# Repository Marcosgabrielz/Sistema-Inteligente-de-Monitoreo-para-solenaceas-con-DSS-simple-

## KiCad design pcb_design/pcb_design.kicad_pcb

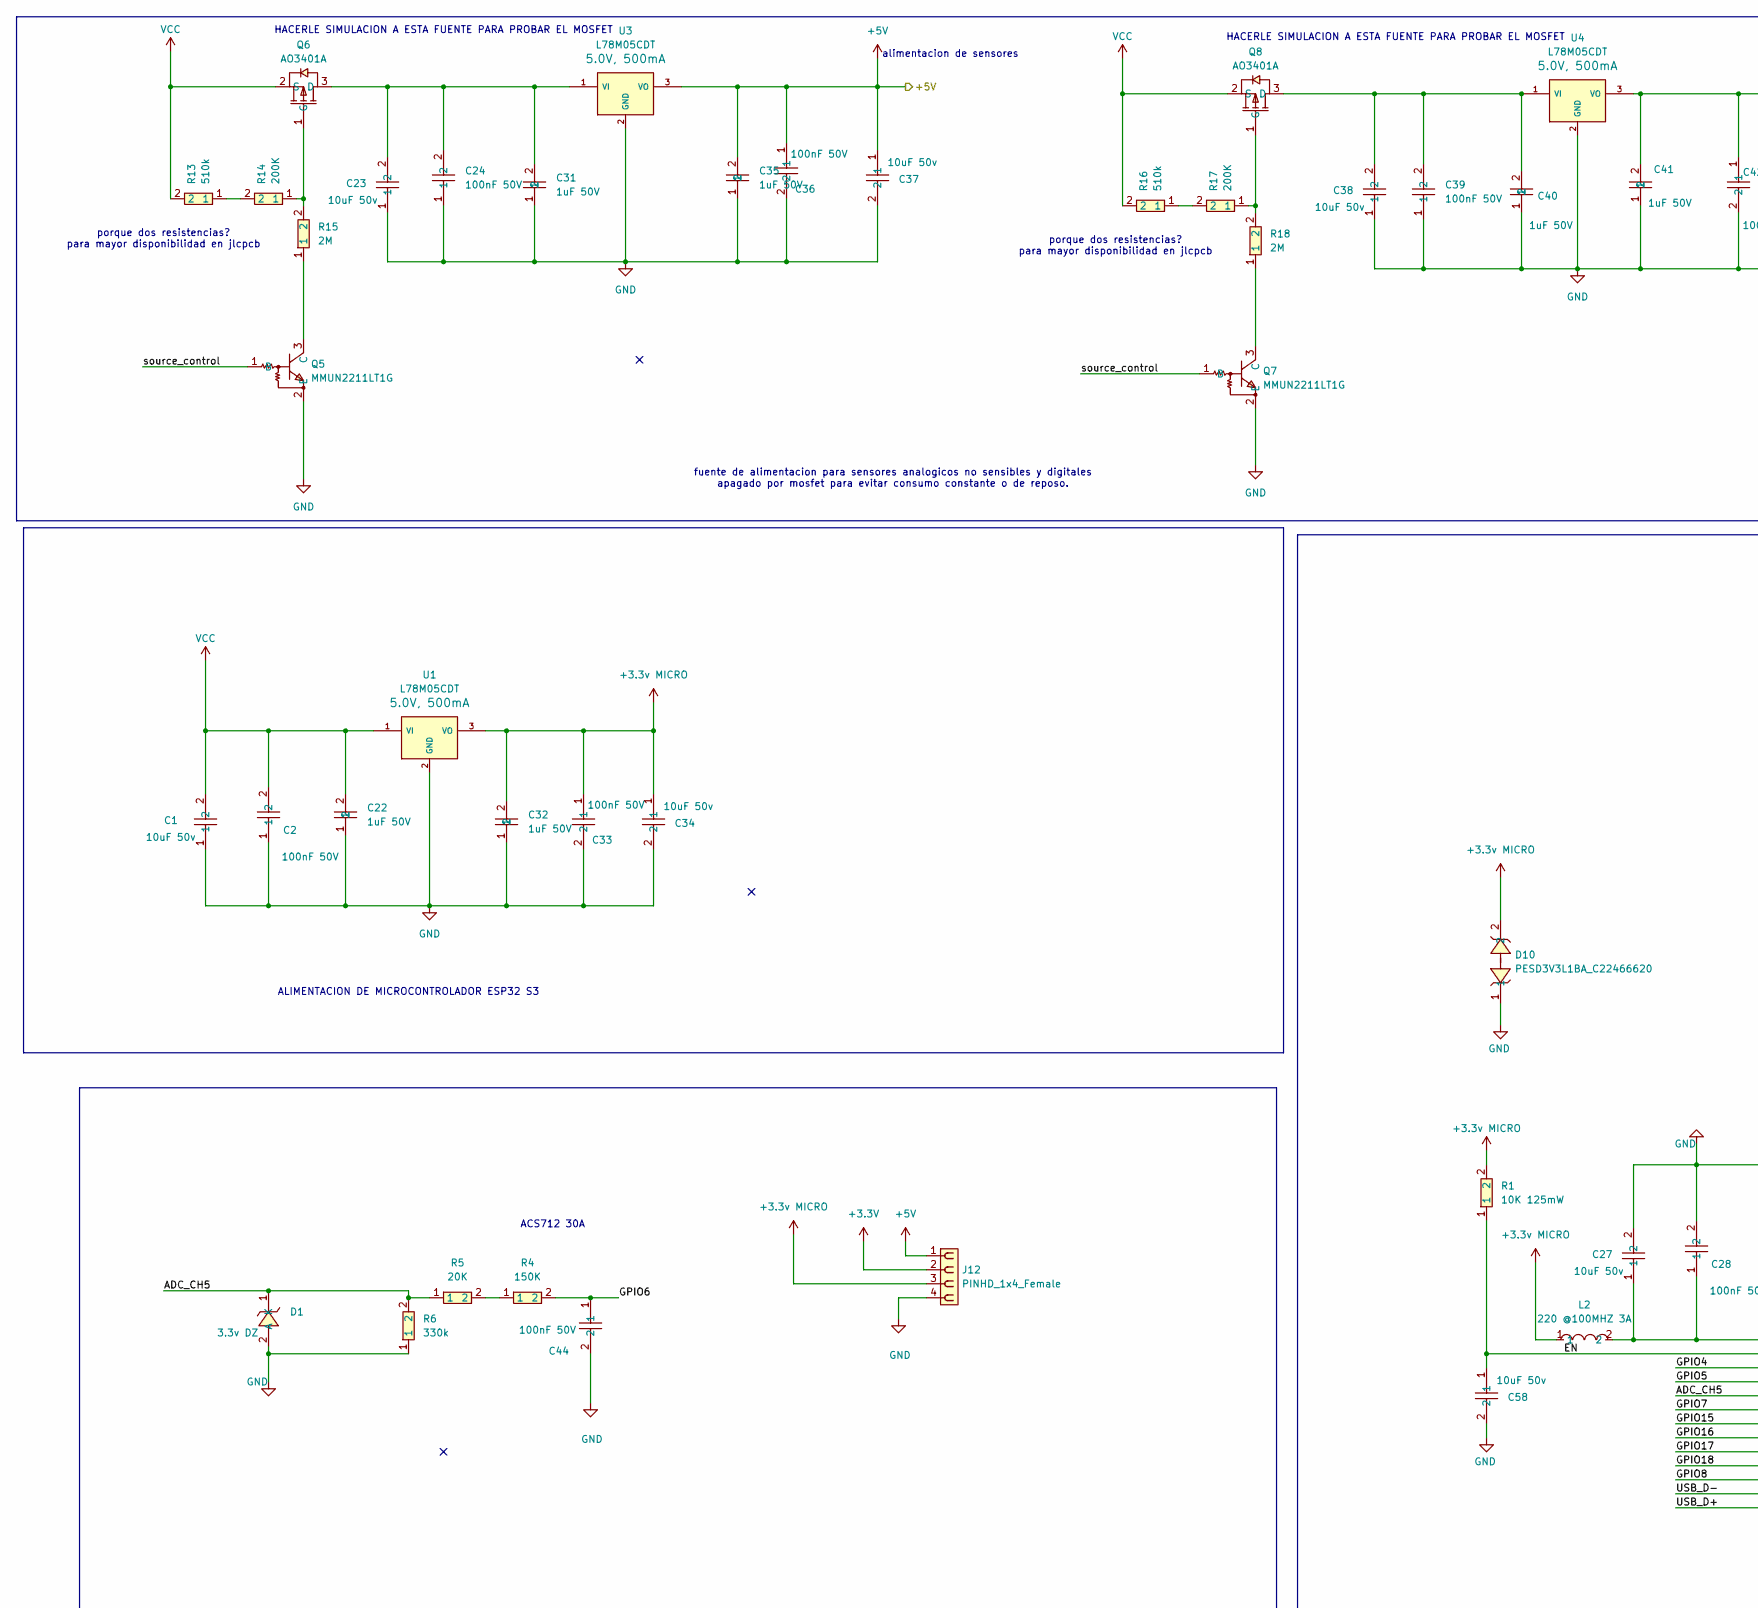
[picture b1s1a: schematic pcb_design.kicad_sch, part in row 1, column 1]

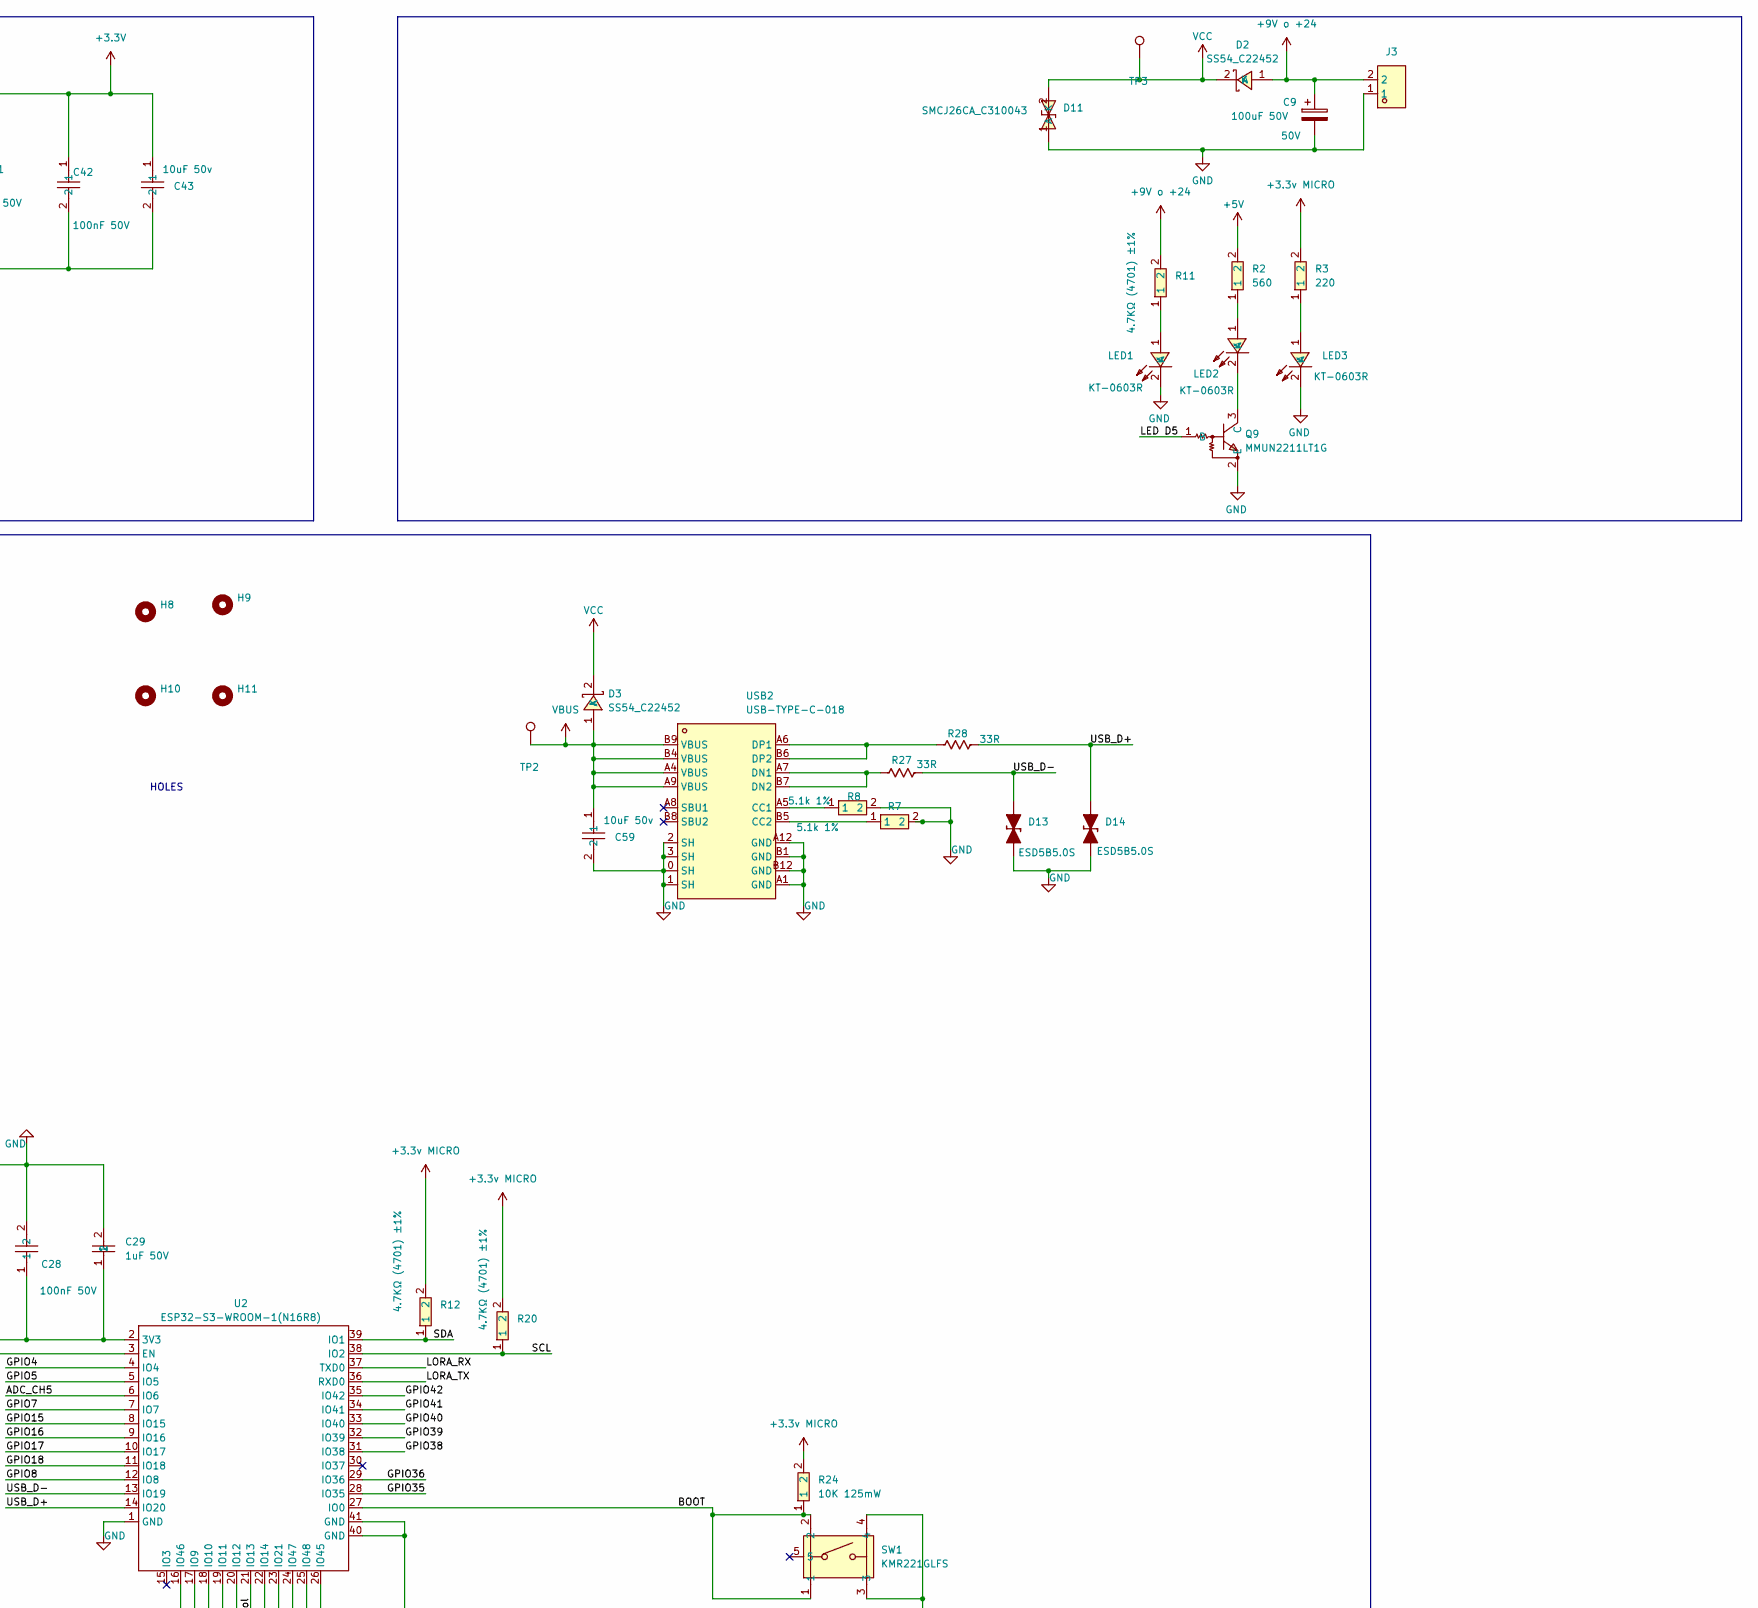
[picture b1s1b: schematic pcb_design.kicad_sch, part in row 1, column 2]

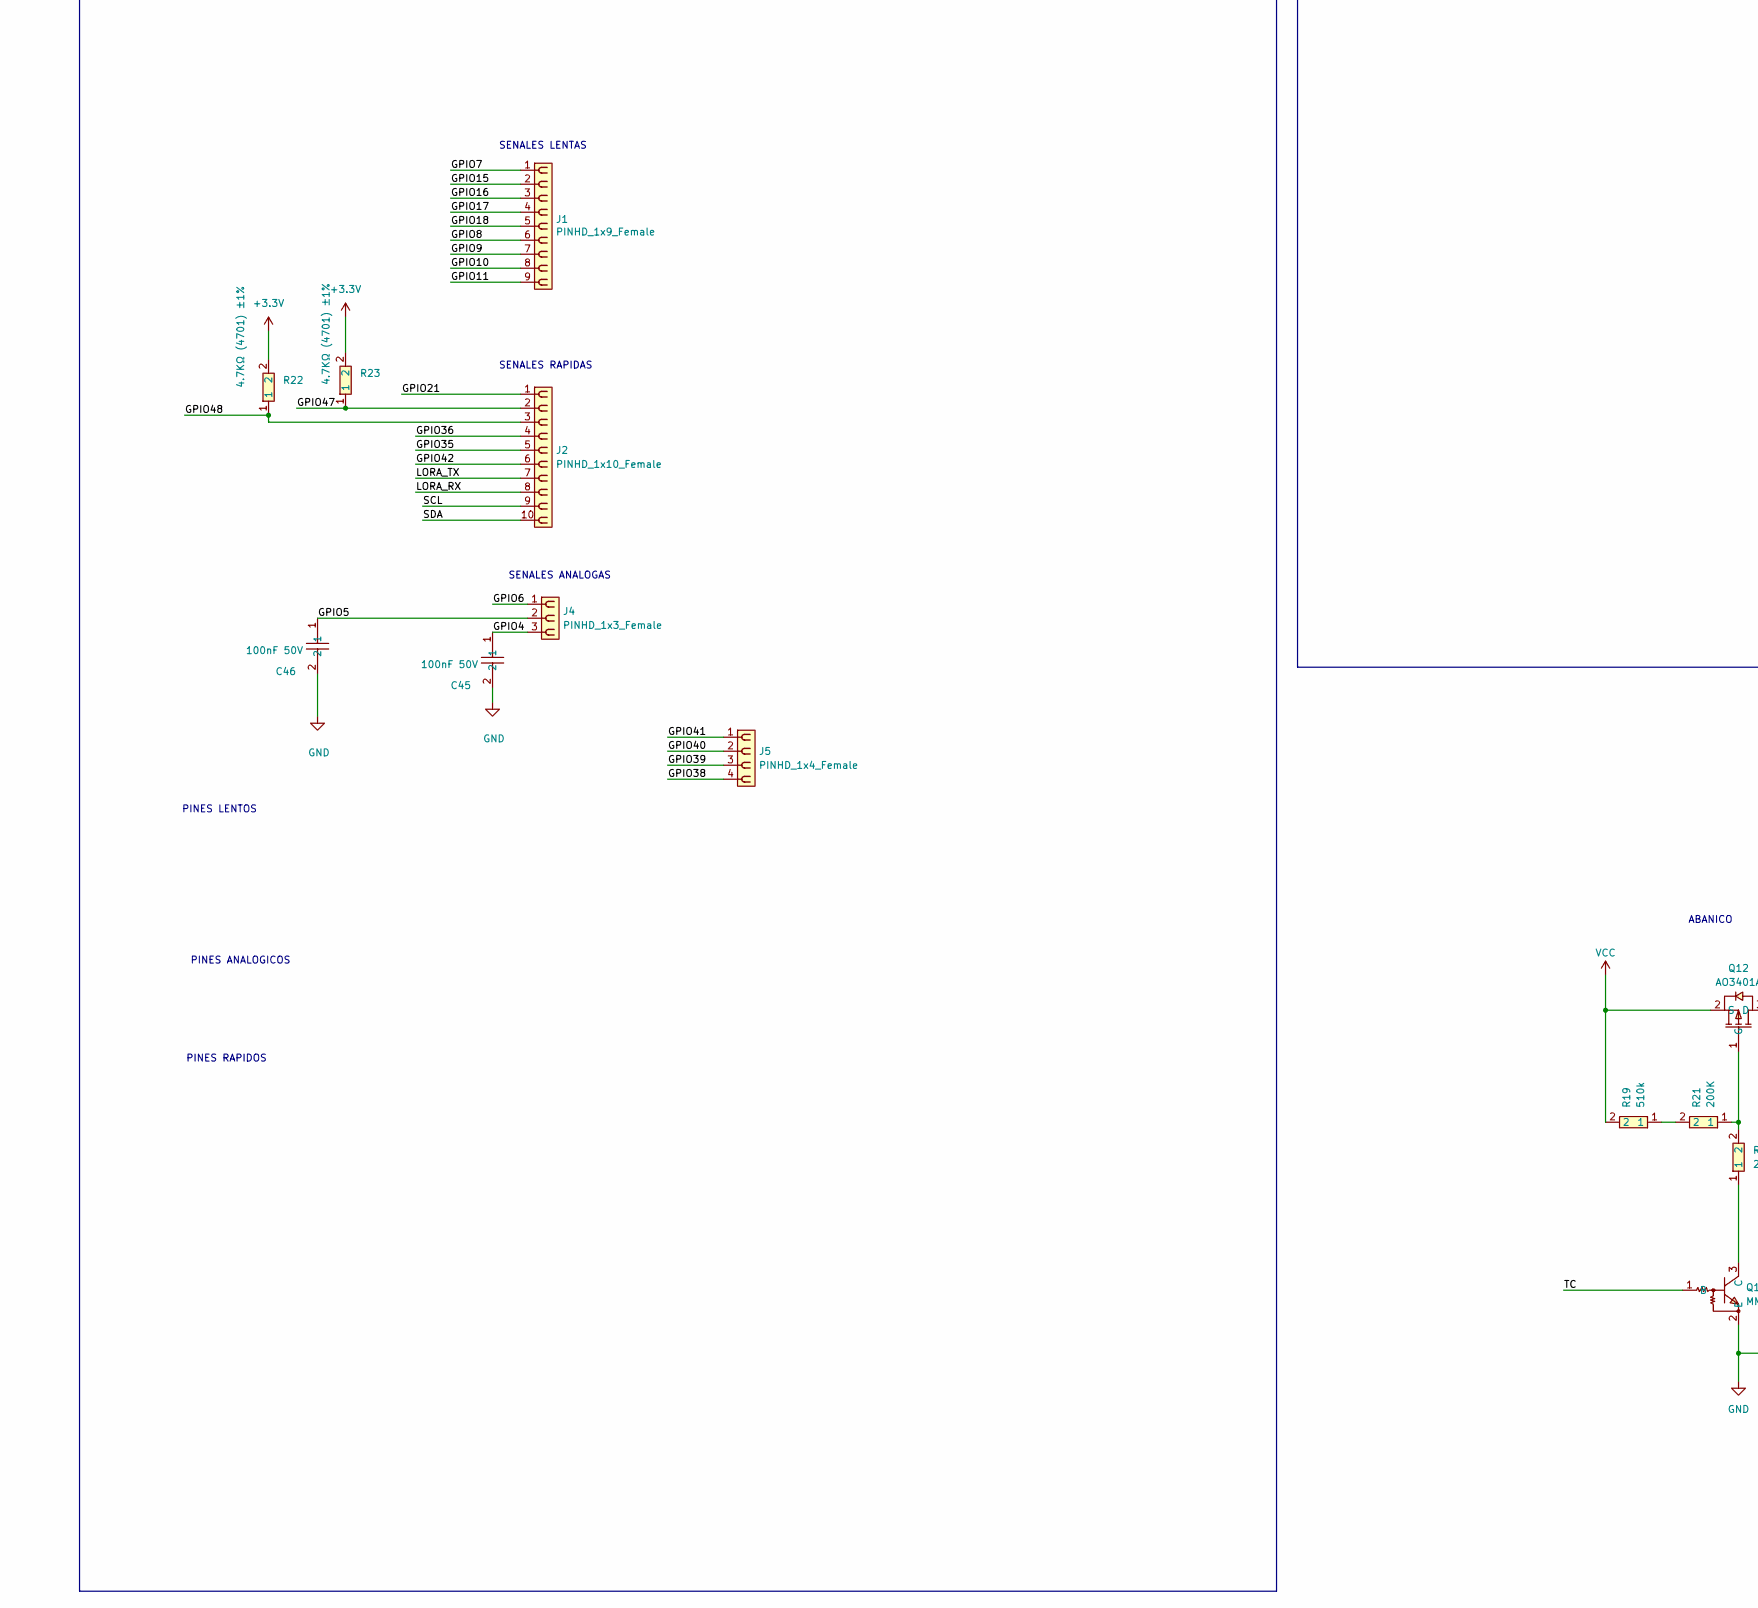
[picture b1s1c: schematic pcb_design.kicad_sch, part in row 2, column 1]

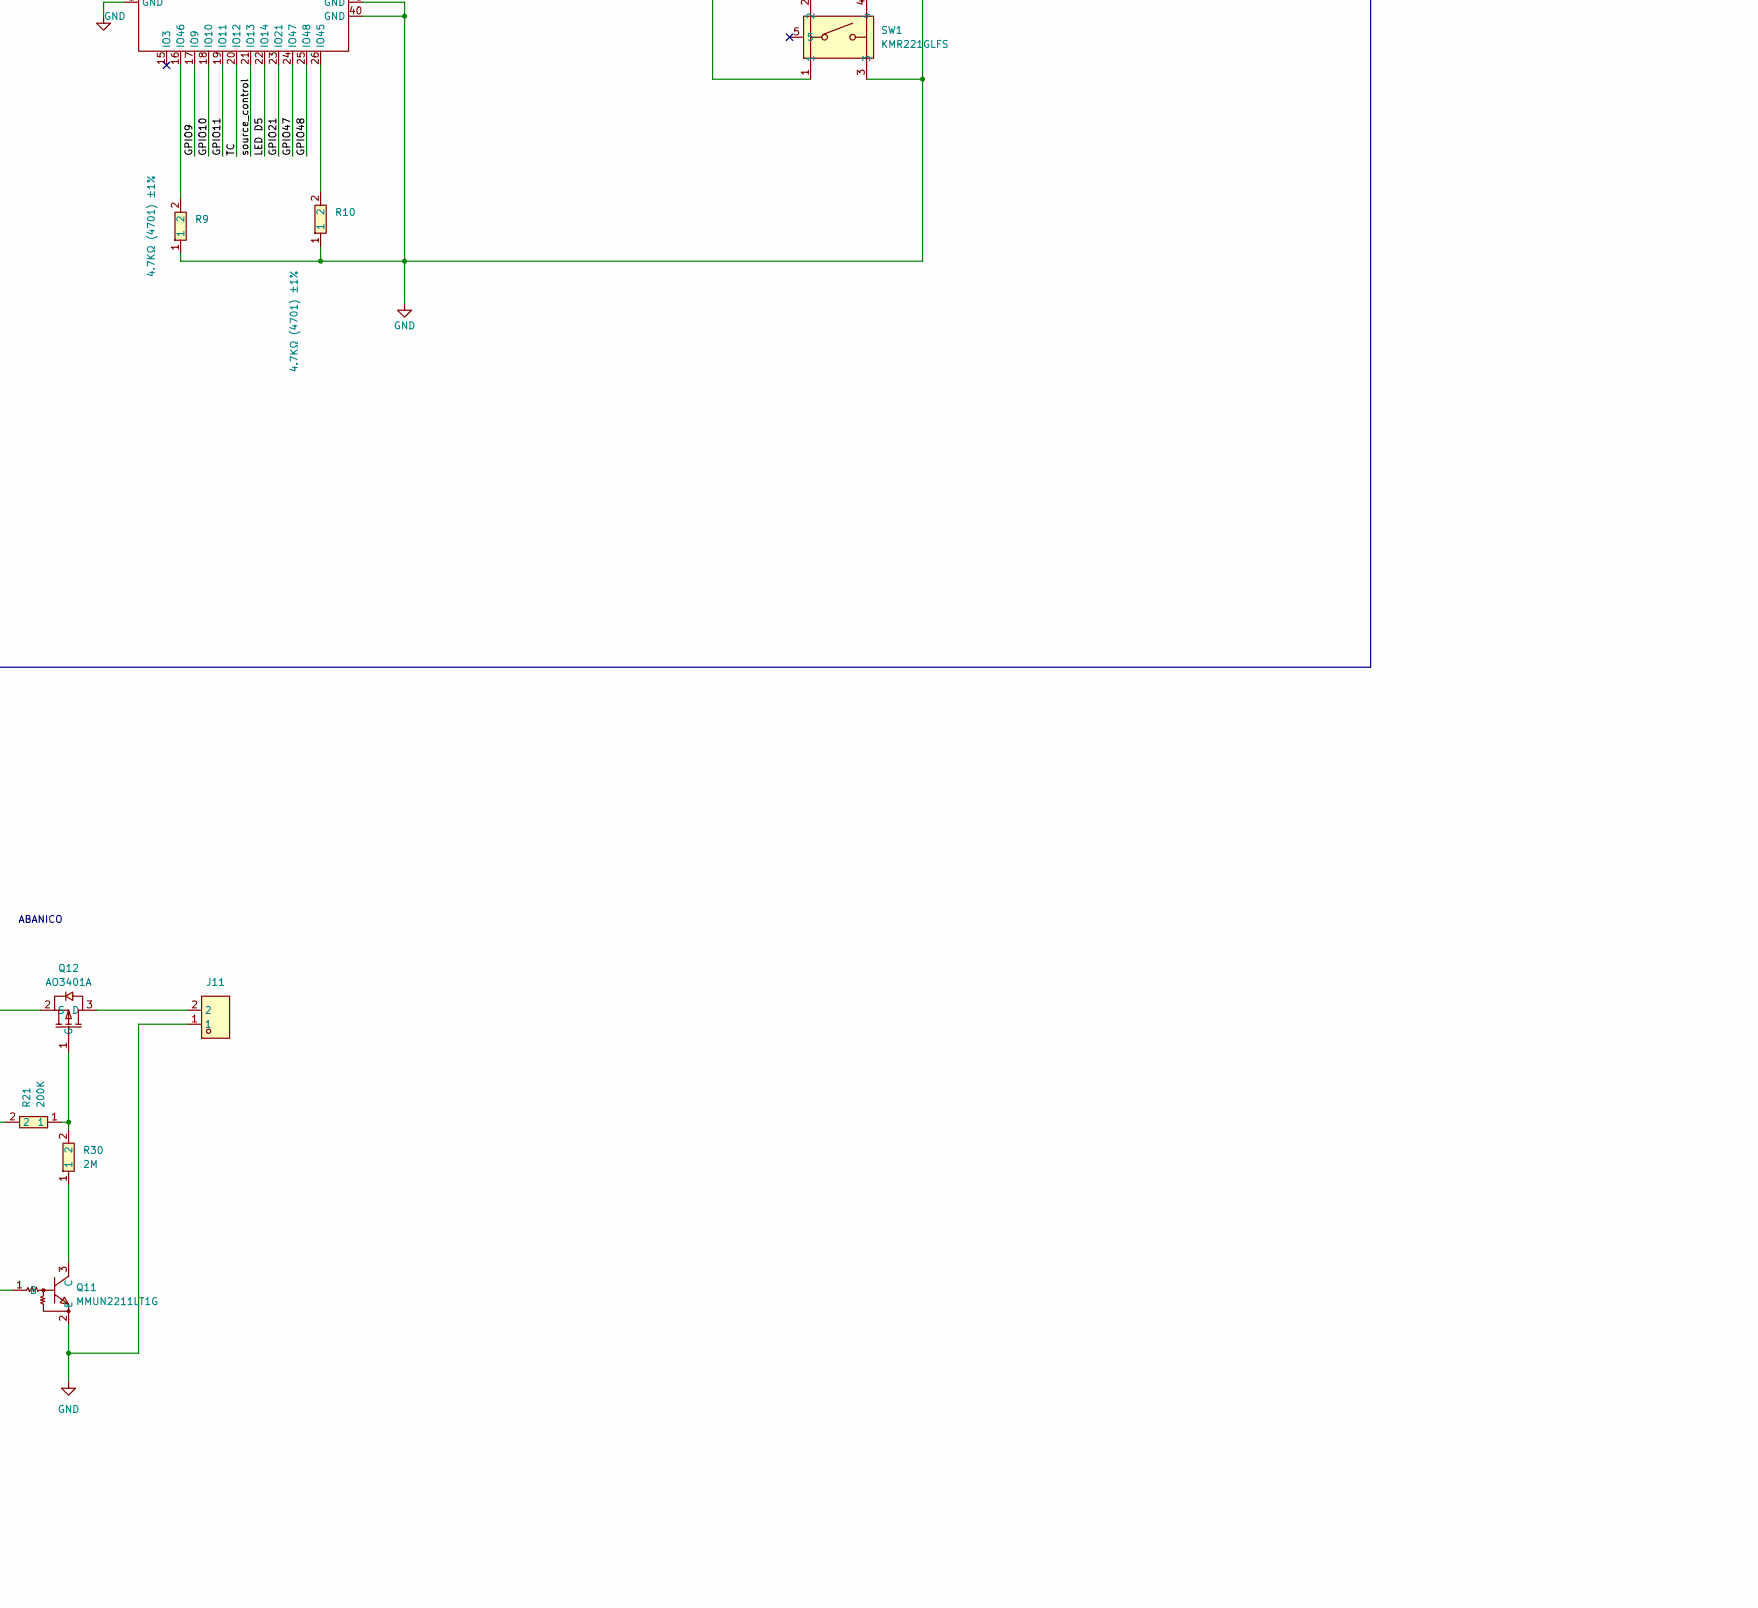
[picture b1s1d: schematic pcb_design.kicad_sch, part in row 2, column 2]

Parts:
C1, C23, C27, C34, C37, C38, C43, C58, C59: 10uF 50v; C0805; MPN GRM21BR61H106KE43L; LCSC Part C440198
C2, C24, C28, C33, C36, C39, C42, C44, C45, C46: 100nF 50V; C0603; MPN CC0603KRX7R9BB104; LCSC Part C14663
C9: 100uF 50V; CP_Radial_D5.0mm_P2.50mm; LCSC Part C3151829
C22, C29, C31, C32, C35, C40, C41: 1uF 50V; C0805; MPN CL21B105KBFNNNE; LCSC Part C28323
D1: MMSZ5226B_C19077421; SOD-123_L2.7-W1.6-LS3.7-RD; MPN MMSZ5226B; LCSC Part C19077421
D2, D3: SS54_C22452; SMA_L4.4-W2.8-LS5.4-R-RD; MPN SS54; LCSC Part C22452
D10: PESD3V3L1BA_C22466620; SOD-323_L1.7-W1.3-LS2.6-BI; MPN PESD3V3L1BA; LCSC Part C22466620
D11: SMCJ26CA_C310043; SMC_L6.9-W5.9-LS7.9-BI; MPN SMCJ26CA/TR13; LCSC Part C310043
D13, D14: ESD5B5.0S; D_SOD-523; LCSC Part C93623
H8, H9, H10, H11: MountingHole; MountingHole_2-56
J1: PINHD_1x9_Female; 1x09_P2.54mm
J2: PINHD_1x10_Female; 1x10_P2.54mm
J3: DB128L-5.08-2P-BK-S; ScrewTerminal_1x02_P5.0mm; LCSC Part C430601
J4: PINHD_1x3_Female; 1x03_P2.54mm
J5, J12: PINHD_1x4_Female; 1x04_P2.54mm
J11: DB128L-5.08-2P-BK-S; 1x02_P2.54mm; LCSC Part C430601
L2: 220 @100MHZ 3A; L0805; MPN MPZ2012S221AT000; LCSC Part C76818
LED1, LED2, LED3: KT-0603R; LED-SMD_L1.6-W0.8-R-RD; MPN KT-0603R; LCSC Part C2286
Q5, Q7, Q9, Q11: MMUN2211LT1G; SOT-23-3_L2.9-W1.6-P1.90-LS2.8-BR; MPN MMUN2211LT1G; LCSC Part C55059
Q6, Q8, Q12: AO3401A; SOT-23_L2.9-W1.3-P1.90-LS2.4-BR; MPN AO3401A; LCSC Part C15127
R1, R24: 10K 125mW; R0805; MPN 0805W8F1002T5E; LCSC Part C17414
R2: 560; R0603; MPN 0603WAF5600T5E; LCSC Part C23204
R3: 220; R0805; MPN 0805W8F2200T5E; LCSC Part C17557
R4: 150K; R0805; MPN 0805W8F1503T5E; LCSC Part C17470
R5: 20K; R0603; MPN 0603WAF2002T5E; LCSC Part C4184
R6: 330k; R0603; MPN 0603WAF3303T5E; LCSC Part C23137
R7, R8: FRC0603F5101TS; R0603; MPN FRC0603F5101TS; LCSC Part C2907044
R9, R10, R11, R12, R20, R22, R23: 0603WAF4701T5E; R0603; MPN 0603WAF4701T5E; LCSC Part C23162
R13, R16, R19: 510k; R0603; MPN 0603WAF5103T5E; LCSC Part C23192
R14, R17, R21: 200K; R0603; MPN 0603WAF2003T5E; LCSC Part C25811
R15, R18, R30: 2M; R0603; MPN 0603WAF2004T5E; LCSC Part C22976
R27, R28: 33R; R_0603_1608Metric; LCSC Part C126353
SW1: KMR221GLFS; KEY-SMD_KMR2XXGXXX; MPN KMR221GLFS; LCSC Part C72443
TP2, TP3: TestPoint_Hole1; TestPoint_WireHole
U1, U3, U4: L78M05CDT; TO-220-3_Vertical; Part Number L78M05CDT-TR; JLCPCB ID C58069
U2: ESP32-S3-WROOM-1(N16R8); WIRELM-SMD_ESP32-S3-WROOM-1; LCSC Part C2913204
USB2: USB-TYPE-C-018; USB-C_SMD-TYPE-C-31-M-12; MPN USB-TYPE-C-018; LCSC Part C2927038

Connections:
+3.3V: C41.2, C42.1, C43.1, J12.2, R22.2, R23.2, U4.3 (VO)
+3.3v MICRO: C32.2, C33.1, C34.1, D10.2, J12.3, L2.1, R1.2, R3.2, R12.2, R20.2, R24.2, U1.3 (VO)
+5V: C35.2, C36.1, C37.1, J12.1, R2.2, U3.3 (VO)
+9V o +24: C9.1, D2.1 (A), J3.2, R11.2
/ADC_CH5: D1.1 (K), R5.1, R6.2, U2.6 (IO6)
/BOOT: R24.1, SW1.1, SW1.2, U2.27 (IO0)
/EN: C58.1, R1.1, U2.3 (EN)
/GPIO4: C45.1, J4.3, U2.4 (IO4)
/GPIO5: C46.1, J4.2, U2.5 (IO5)
/GPIO6: C44.1, J4.1, R4.2
/GPIO7: J1.1, U2.7 (IO7)
/GPIO8: J1.6, U2.12 (IO8)
/GPIO9: J1.7, U2.17 (IO9)
/GPIO10: J1.8, U2.18 (IO10)
/GPIO11: J1.9, U2.19 (IO11)
/GPIO15: J1.2, U2.8 (IO15)
/GPIO16: J1.3, U2.9 (IO16)
/GPIO17: J1.4, U2.10 (IO17)
/GPIO18: J1.5, U2.11 (IO18)
/GPIO21: J2.1, U2.23 (IO21)
/GPIO35: J2.5, U2.28 (IO35)
/GPIO36: J2.4, U2.29 (IO36)
/GPIO38: J5.4, U2.31 (IO38)
/GPIO39: J5.3, U2.32 (IO39)
/GPIO40: J5.2, U2.33 (IO40)
/GPIO41: J5.1, U2.34 (IO41)
/GPIO42: J2.6, U2.35 (IO42)
/GPIO47: J2.2, R23.1, U2.24 (IO47)
/GPIO48: J2.3, R22.1, U2.25 (IO48)
/LED D5: Q9.1 (B), U2.22 (IO14)
/LORA_RX: J2.8, U2.37 (TXD0)
/LORA_TX: J2.7, U2.36 (RXD0)
/SCL: J2.9, R20.1, U2.38 (IO2)
/SDA: J2.10, R12.1, U2.39 (IO1)
/TC: Q11.1 (B), U2.20 (IO12)
/USB_D+: D14.2 (A), R28.2, U2.14 (IO20)
/USB_D-: D13.2 (A), R27.2, U2.13 (IO19)
/source_control: Q5.1 (B), Q7.1 (B), U2.21 (IO13)
GND: C1.1, C2.1, C9.2, C22.1, C23.1, C24.1, C27.2, C28.2, C29.2, C31.1, C32.1, C33.2, C34.2, C35.1, C36.2, C37.2, C38.1, C39.1, C40.1, C41.1, C42.2, C43.2, C44.2, C45.2, C46.2, C58.2, C59.2, D1.2 (A), D10.1, D11.1 (K), D13.1 (K), D14.1 (K), J3.1, J11.1, J12.4, LED1.2 (K), LED3.2 (K), Q5.2 (E), Q7.2 (E), Q9.2 (E), Q11.2 (E), R6.1, R7.2, R8.2, R9.1, R10.1, SW1.3, SW1.4, U1.2 (GND), U2.1 (GND), U2.40 (GND), U2.41 (GND), U3.2 (GND), U4.2 (GND), USB2.0 (SH), USB2.1 (SH), USB2.2 (SH), USB2.3 (SH), USB2.A1 (GND), USB2.A12 (GND), USB2.B1 (GND), USB2.B12 (GND)
unnamed: LED1.1 (A), R11.1
unnamed: LED2.1 (A), R2.1
unnamed: LED2.2 (K), Q9.3 (C)
unnamed: LED3.1 (A), R3.1
unnamed: Q5.3 (C), R15.1
unnamed: C23.2, C24.2, C31.2, Q6.3 (D), U3.1 (VI)
unnamed: Q6.1 (G), R14.1, R15.2
unnamed: Q7.3 (C), R18.1
unnamed: C38.2, C39.2, C40.2, Q8.3 (D), U4.1 (VI)
unnamed: Q8.1 (G), R17.1, R18.2
unnamed: Q11.3 (C), R30.1
unnamed: J11.2, Q12.3 (D)
unnamed: Q12.1 (G), R21.1, R30.2
unnamed: R4.1, R5.2
unnamed: R13.1, R14.2
unnamed: R16.1, R17.2
unnamed: R19.1, R21.2
unnamed: C27.1, C28.1, C29.1, L2.2, U2.2 (3V3)
unnamed: R10.2, U2.26 (IO45)
unnamed: R9.2, U2.16 (IO46)
unnamed: R8.1, USB2.A5 (CC1)
unnamed: R7.1, USB2.B5 (CC2)
unnamed: R27.1, USB2.A7 (DN1), USB2.B7 (DN2)
unnamed: R28.1, USB2.A6 (DP1), USB2.B6 (DP2)
VBUS: C59.1, D3.1 (A), TP2.1 (1_1), USB2.A4 (VBUS), USB2.A9 (VBUS), USB2.B4 (VBUS), USB2.B9 (VBUS)
VCC: C1.2, C2.2, C22.2, D2.2 (K), D3.2 (K), D11.2 (A), Q6.2 (S), Q8.2 (S), Q12.2 (S), R13.2, R16.2, R19.2, TP3.1 (1_1), U1.1 (VI)

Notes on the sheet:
HOLES
HACERLE SIMULACION A ESTA FUENTE PARA PROBAR EL MOSFET
PINES ANALOGICOS
SENALES ANALOGAS
SENALES LENTAS
SENALES RAPIDAS
alimentacion de sensores
PINES LENTOS
ALIMENTACION DE MICROCONTROLADOR ESP32 S3
fuente de alimentacion para sensores analogicos no sensibles y digitales apagado por mosfet para evitar consumo constante o de reposo.
ACS712 30A
PINES RAPIDOS
porque dos resistencias? para mayor disponibilidad en jlcpcb
ABANICO

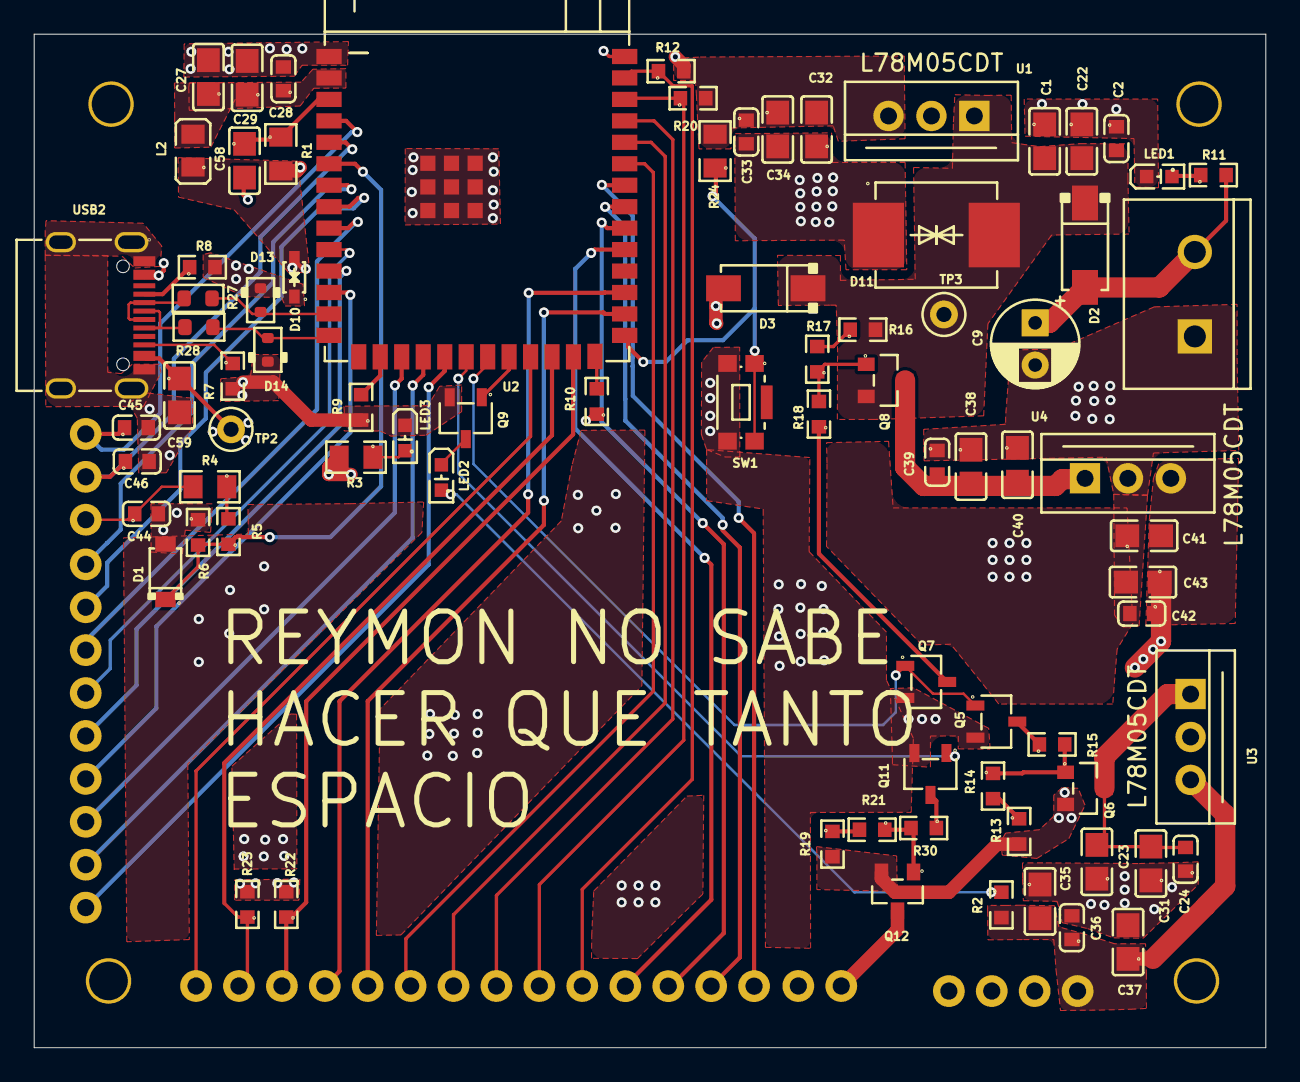
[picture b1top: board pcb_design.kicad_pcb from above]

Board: 4 copper layers, 72.9 x 60.0 mm, 91 parts (0 on the bottom side), 65 nets.
